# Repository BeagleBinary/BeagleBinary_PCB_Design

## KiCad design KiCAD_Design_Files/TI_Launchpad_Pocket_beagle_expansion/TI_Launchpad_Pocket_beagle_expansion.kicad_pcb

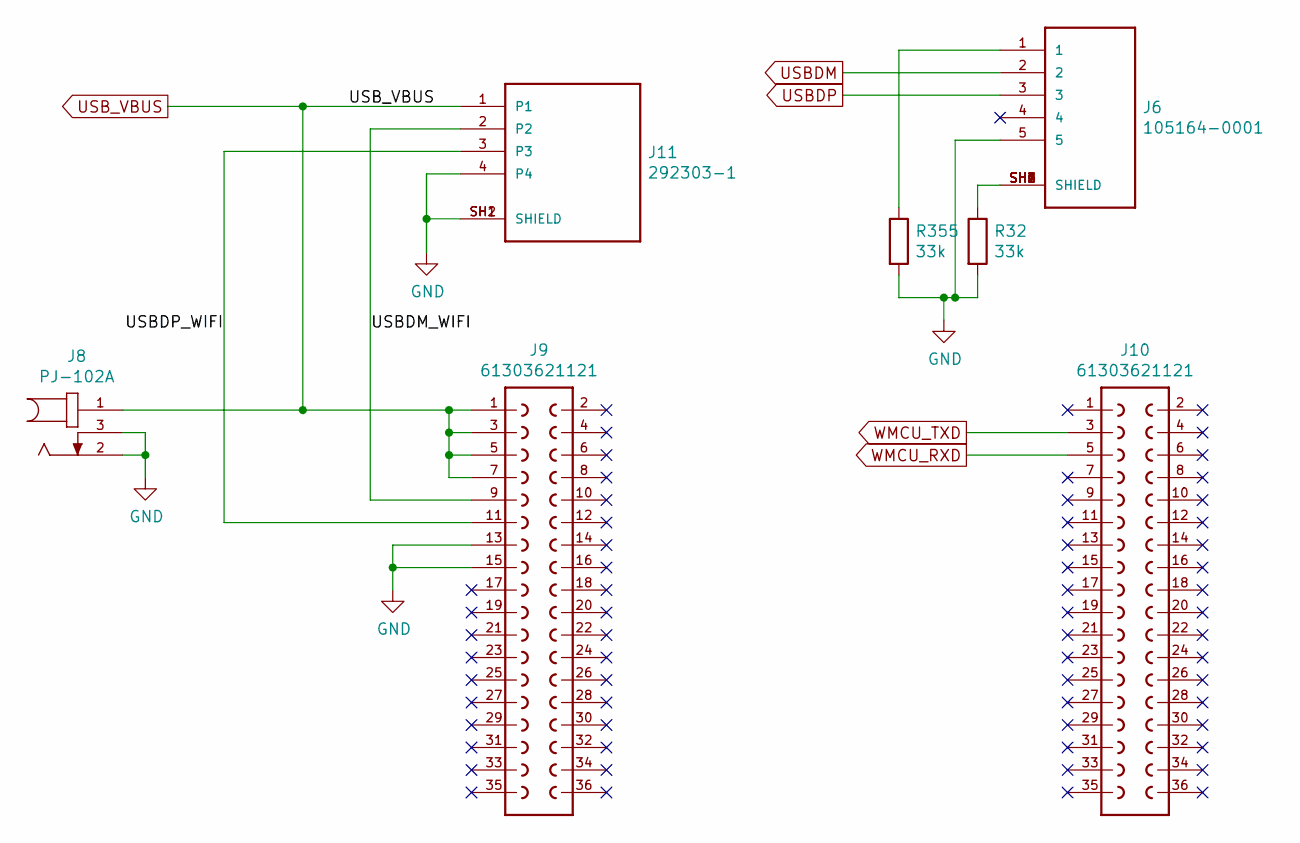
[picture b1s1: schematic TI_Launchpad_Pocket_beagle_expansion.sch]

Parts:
J6: 105164-0001; MOLEX_105164-0001
J8: PJ-102A; CUI_PJ-102A
J9, J10: 61303621121
J11: 292303-1; TE_292303-1
R32, R355: 33k; R_0402_1005Metric

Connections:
/USBDM_WIFI: J9.9 (5), J11.2
/USBDP_WIFI: J9.11 (6), J11.3
GND: J6.5, J8.2, J8.3, J9.13 (7), J9.15 (8), J11.4, J11.SH1 (SHIELD), J11.SH2 (SHIELD), R32.2, R355.2
unnamed: J6.1, R355.1
unnamed: J6.SH1 (SHIELD), J6.SH2 (SHIELD), J6.SH3 (SHIELD), J6.SH4 (SHIELD), J6.SH5 (SHIELD), J6.SH6 (SHIELD), R32.1
USBDM: J6.2
USBDP: J6.3
USB_VBUS: J8.1, J9.1, J9.3 (2), J9.5 (3), J9.7 (4), J11.1
WMCU_RXD: J10.5 (3)
WMCU_TXD: J10.3 (2)

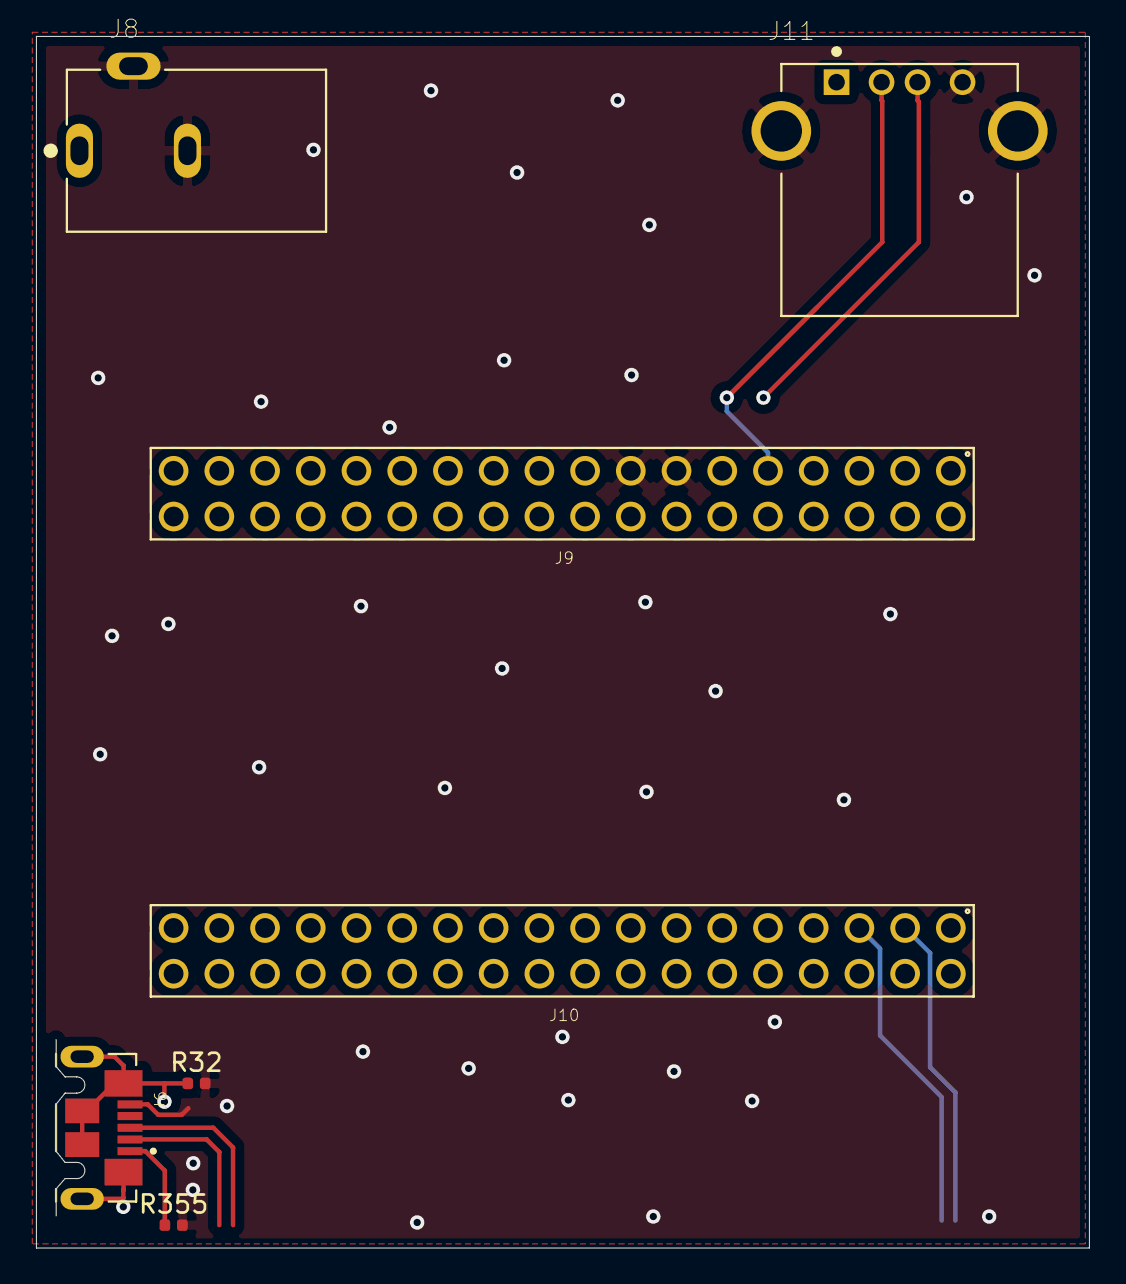
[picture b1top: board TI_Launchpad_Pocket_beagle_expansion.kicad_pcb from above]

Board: 4 copper layers, 58.5 x 67.3 mm, 7 parts (0 on the bottom side), 6 nets.
